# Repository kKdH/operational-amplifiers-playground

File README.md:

# Operational Amplifiers Playground

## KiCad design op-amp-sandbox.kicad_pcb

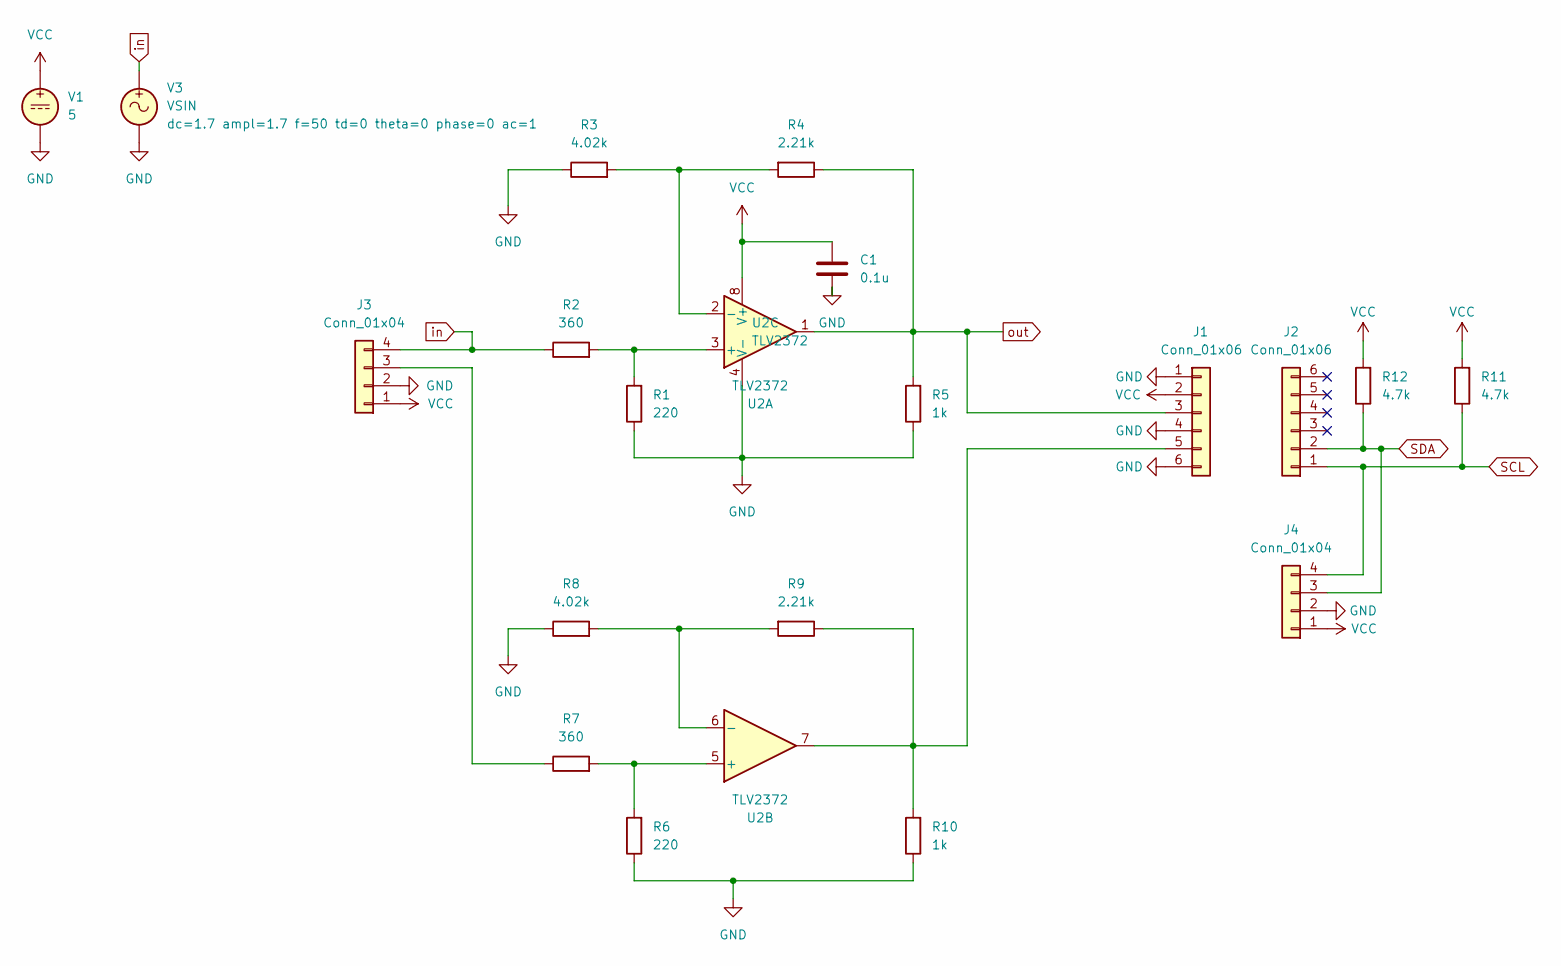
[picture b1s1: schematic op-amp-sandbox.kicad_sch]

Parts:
C1: 0.1u; C_0805_2012Metric
J1, J2: Conn_01x06; PinSocket_1x06_P2.54mm_Vertical
J3: Conn_01x04; PinHeader_1x04_P2.54mm_Vertical
J4: Conn_01x04; PinHeader_1x04_P2.54mm_Horizontal
R1, R6: 220; R_1206_3216Metric
R2, R7: 360; R_1206_3216Metric
R3, R8: 4.02k; R_1206_3216Metric
R4, R9: 2.21k; R_1206_3216Metric
R5, R10: 1k; R_1206_3216Metric
R11, R12: 4.7k; R_1206_3216Metric
U2: TLV2372; P8
V1: 5
V3: VSIN

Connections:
GND: C1.2, J1.1, J1.4, J1.6, J3.2, J4.2, R1.1, R3.1, R5.1, R6.1, R8.1, R10.1, U2.4 (V-), V1.2, V3.2
unnamed: J1.5, R9.1, R10.2, U2.7
unnamed: J3.3, R7.1
unnamed: R1.2, R2.2, U2.3 (+)
unnamed: R3.2, R4.2, U2.2 (-)
unnamed: R6.2, R7.2, U2.5 (+)
unnamed: R8.2, R9.2, U2.6 (-)
SCL: J2.1, J4.4, R11.1
SDA: J2.2, J4.3, R12.1
VCC: C1.1, J1.2, J3.1, J4.1, R11.2, R12.2, U2.8 (V+), V1.1
in: J3.4, R2.1, V3.1
out: J1.3, R4.1, R5.2, U2.1

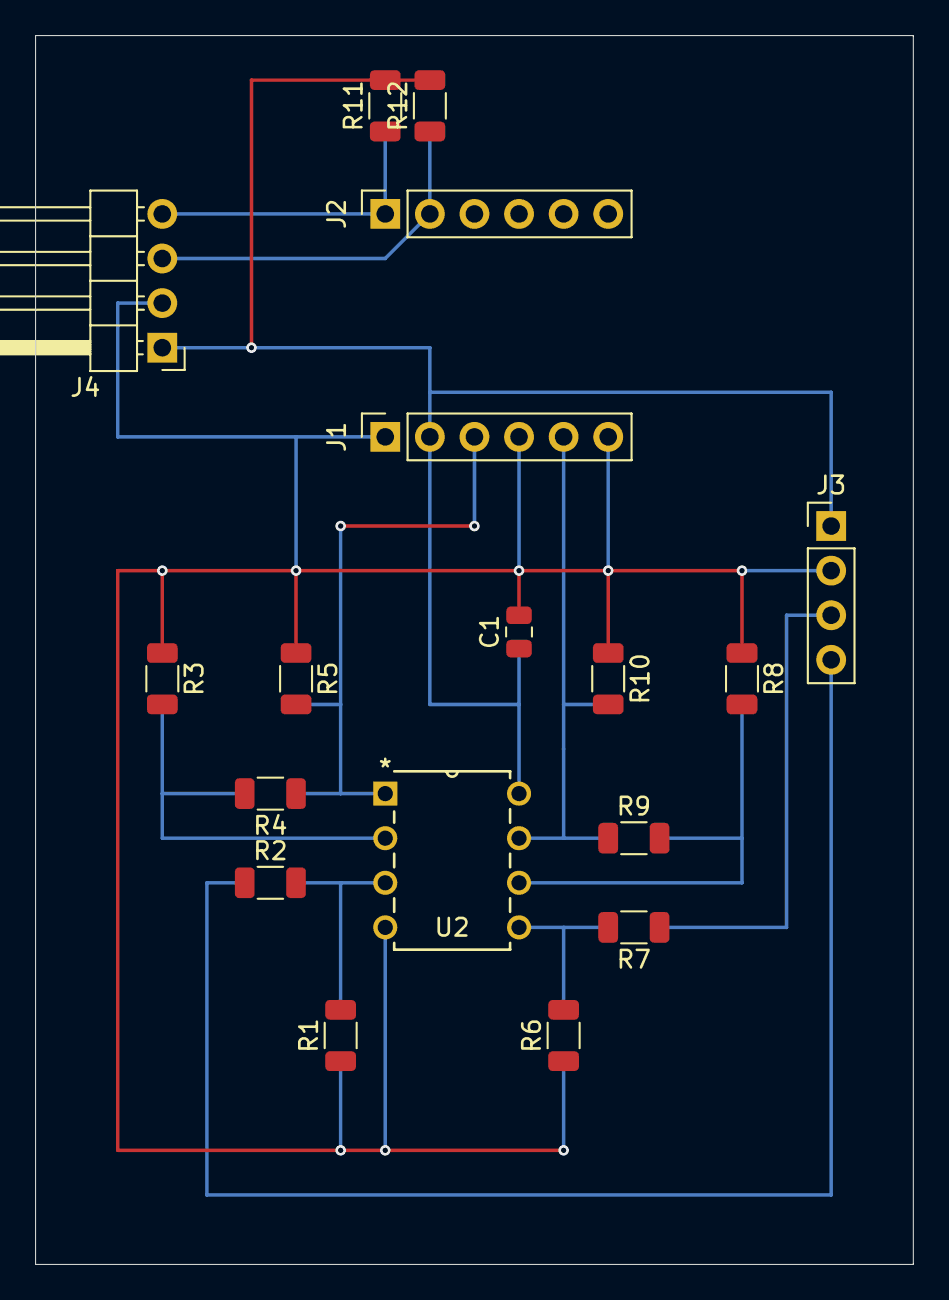
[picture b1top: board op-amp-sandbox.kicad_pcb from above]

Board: 2 copper layers, 50.0 x 70.0 mm, 18 parts (0 on the bottom side), 12 nets.

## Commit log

2024-09-23 Initial commit.
2024-09-23 Initial design.
2024-09-29 Added lock files to .gitignore.
2024-09-29 Added additional pin headers to the board.
